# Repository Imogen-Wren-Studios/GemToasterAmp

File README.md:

# GemToasterAmp
 9v to 12v Battery Powered Amp

 _LM386 Based power amp with JFET Preamp_

 - Quality of sound highly dependent on speaker & cab combo.
 
 ## 3D Model
 #### Iso
  
 #### Underside
 
 #### Topside

 ## PCB Layout

 ## Schematic

 ### JFET Selection
 
 _I thought there were some notes on this but I can't find them, the only other thing I had read says "Anything Goes". They used cheapo out of spec parts and they worked._
 
### Other Parts slection

Some parts can be more difficult to find or I just didnt have them in stock for my test build, so these are the values I used in my *working* build:
 
 3.9k Resistors - 15k in parallel with 5.1k
 4.3k Resistors - 15k in  parallel  with 6.2k

470n Capacitor - 390n Could put an additional 100n in parallel to get closer to marked value

15n Capacitor - 22n

## Revision 0 Issues:
- Power Amp control is backwards, but this control isnt that useable, on the origional project this was replaced with a trimpot anyway, so suggest mounting it back to front for a "set and forget" control, or replace with fixed value resistor.
   - Could also look into cutting traces between 2 and 3 - TODO

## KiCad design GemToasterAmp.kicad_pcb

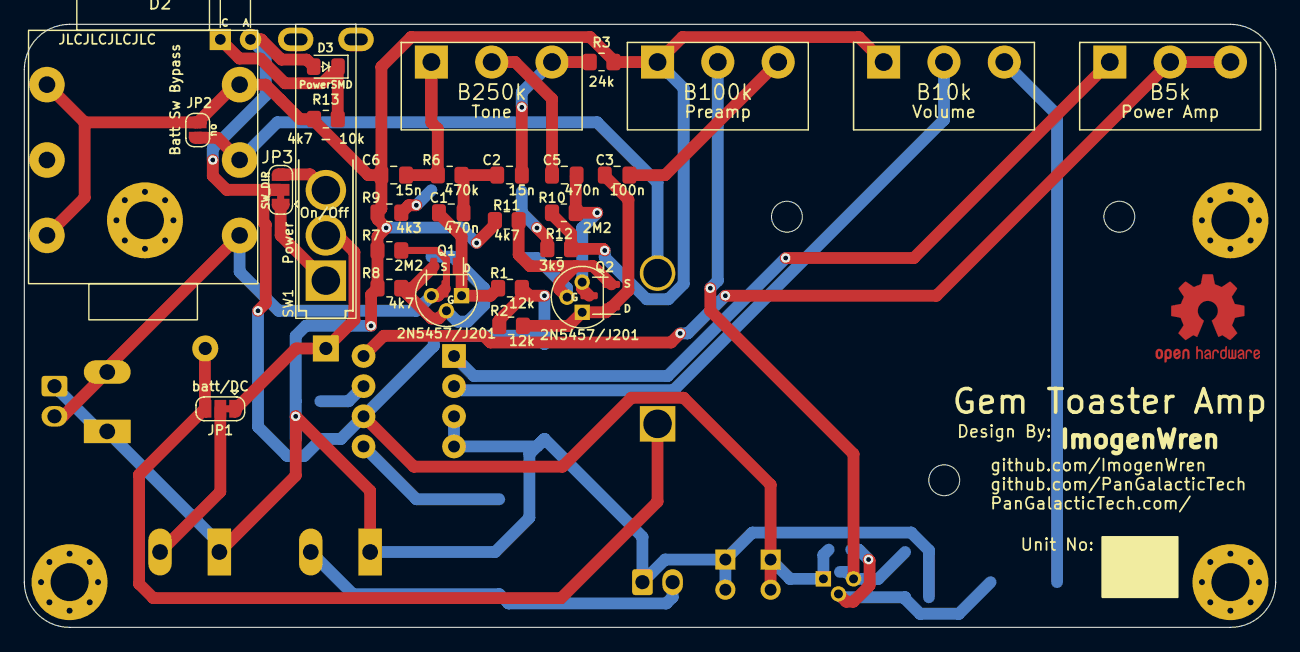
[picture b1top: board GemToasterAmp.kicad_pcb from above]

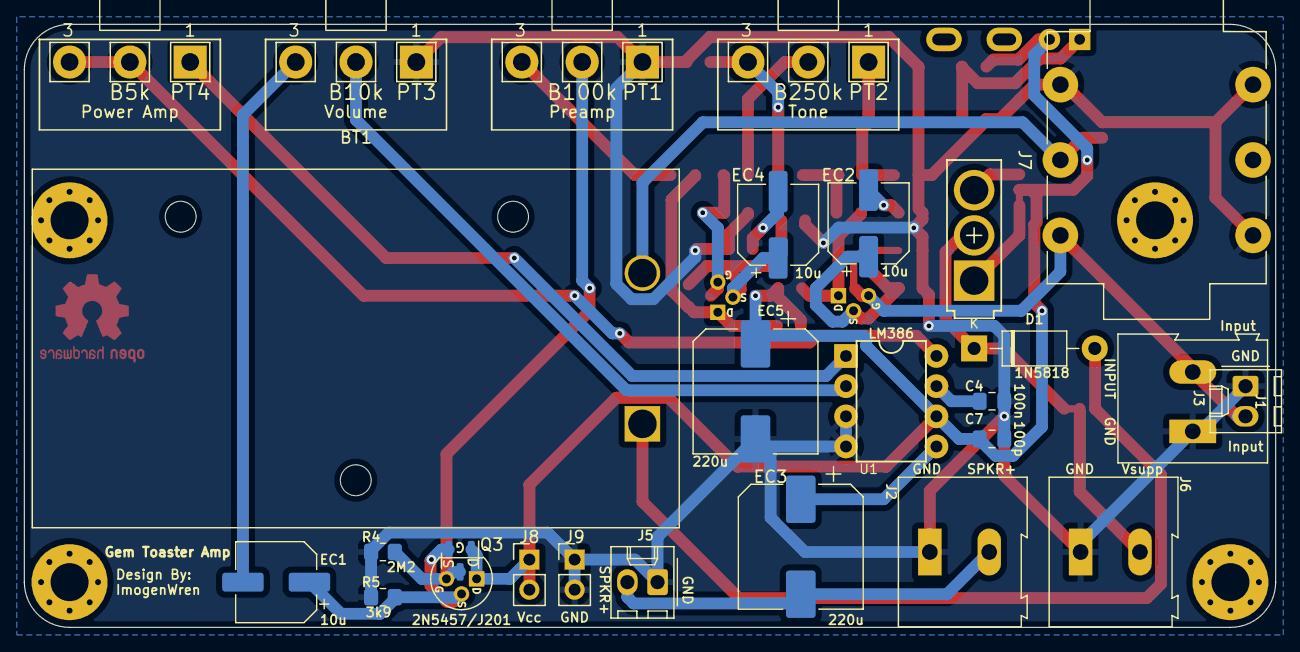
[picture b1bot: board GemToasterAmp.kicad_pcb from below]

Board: 2 copper layers, 105.4 x 50.8 mm, 49 parts (25 on the bottom side), 31 nets.

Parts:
BT1: 9v Battery; BatteryHolder_Eagle_12BH611-GR
C1, C5: 470n; C_0805_2012Metric_Pad1.18x1.45mm_HandSolder
C2, C6: 15n; C_0805_2012Metric_Pad1.18x1.45mm_HandSolder
C3, C4: 100n; C_0805_2012Metric_Pad1.18x1.45mm_HandSolder
C7: 100p; C_0805_2012Metric_Pad1.18x1.45mm_HandSolder
D1: 1N5818; D_DO-41_SOD81_P10.16mm_Horizontal
D2: PowerTH; LED_D5.0mm_Flat
D3: PowerSMD; LED_0805_2012Metric_Pad1.15x1.40mm_HandSolder
EC1, EC2, EC4: 10u; CP_Elec_6.3x5.9
EC3, EC5: 220u; CP_Elec_10x10
J1: Input; TerminalBlock_Altech_AK300-2_P5.00mm
J2: Speaker(2-8 ohm); TerminalBlock_Altech_AK300-2_P5.00mm
J3: Input; Molex_KK-254_AE-6410-02A_1x02_P2.54mm_Vertical_copy
J5: Speaker; Molex_KK-254_AE-6410-02A_1x02_P2.54mm_Vertical_copy
J6: Power; TerminalBlock_Altech_AK300-2_P5.00mm
J7: AudioJack3_Switch; Jack_6.35mm_Neutrik_NMJ6HFD2_Horizontal
J8: Vcc; PinHeader_1x02_P2.54mm_Vertical
J9: GND; PinHeader_1x02_P2.54mm_Vertical
JP1: batt/DC; SolderJumper-3_P1.3mm_Bridged12_RoundedPad1.0x1.5mm
JP2: Batt Sw Bypass; SolderJumper-2_P1.3mm_Open_RoundedPad1.0x1.5mm
JP3: SW_DIR; SolderJumper-3_P1.3mm_Bridged12_RoundedPad1.0x1.5mm
PT1: B100k; 16MM_AngleMount
PT2: B250k; 16MM_AngleMount
PT3: B10k; 16MM_AngleMount
PT4: B5k; 16MM_AngleMount
Q1, Q2, Q3: 2N5457/J201; JFET Dual Foot
R1, R2: 12k; Resistor_0805_2012_handsolder
R3: 24k; Resistor_0805_2012_handsolder
R4, R7, R10: 2M2; Resistor_0805_2012_handsolder
R5, R12: 3k9; Resistor_0805_2012_handsolder
R6: 470k; Resistor_0805_2012_handsolder
R8, R11: 4k7; Resistor_0805_2012_handsolder
R9: 4k3; Resistor_0805_2012_handsolder
R13: 4k7 - 10k; Resistor_0805_2012_handsolder
SW1: On/Off; SPDT-100SP4T1-Right-Angle
U1: LM386; DIL8

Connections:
+BATT: BT1.1 (+), D1.2 (A), JP1.3 (B)
-BATT: BT1.2 (-), J7.R, JP2.2 (B)
/INPUT: J1.2, J3.2, J7.T, Q1.3 (G), R7.1
/SPKR+: EC3.2, J2.2, J5.2
/Vsupp: J6.2, JP1.2 (C)
/power_in: D1.1 (K), JP1.1 (A), SW1.2 (B)
GND: C4.1, C6.2, C7.2, EC5.2, J1.1, J2.1, J3.1, J5.1, J6.1, J7.S, J7.SN, J7.TN, J9.1, J9.2, JP2.1 (A), PT1.1, PT3.1, R3.2, R4.2, R5.2, R7.2, R8.2, R9.2, R10.2, R11.2, R12.2, R13.1, U1.3 (+), U1.4 (GND)
unnamed: C1.1, Q1.1 (D), R1.2
unnamed: C1.2, C2.2, R6.1
unnamed: C2.1, PT2.3, R3.1
unnamed: C3.1, Q2.1 (D), R2.2
unnamed: C3.2, PT1.3
unnamed: C4.2, U1.7 (BYPASS)
unnamed: C5.1, PT2.2
unnamed: C5.2, Q2.3 (G), R10.1
unnamed: C6.1, PT2.1, R6.2
unnamed: D2.1 (K), D3.1 (K), R13.2
unnamed: EC1.1, Q3.2 (S), R5.1
unnamed: EC1.2, PT3.3
unnamed: EC2.1, Q1.2 (S), R8.1
unnamed: EC2.2, R9.1
unnamed: EC3.1, U1.5
unnamed: EC4.1, Q2.2 (S), R11.1
unnamed: EC4.2, R12.1
unnamed: PT1.2, Q3.3 (G), R4.1
unnamed: PT3.2, U1.2 (-)
unnamed: PT4.1, U1.1 (GAIN)
unnamed: PT4.2, PT4.3, U1.8 (GAIN)
unnamed: JP3.1 (A), SW1.1 (A)
unnamed: JP3.3 (B), SW1.3 (C)
VCC: C7.1, D2.2 (A), D3.2 (A), EC5.1, J8.1, J8.2, JP3.2 (C), Q3.1 (D), R1.1, R2.1, U1.6 (V+)

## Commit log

2022-12-16 asdfsd
2022-12-17 57rty
2022-12-18 vjghdfjghf
2022-12-19 dgfhfgh
2022-12-21 layout v0.1
2022-12-21 erfdrgd
2022-12-30 dfgdfgg
2022-12-31 vghnjghj
2023-01-02 dfgdfgd
2023-01-02 yrfthd
2023-01-02 KJIXCSJIDISDS
2023-01-12 dfgfg
2023-02-02 sadf
2023-02-02 added gerbers
2023-02-02 gvhjng
2023-05-26 backup
2025-01-22 moving laptop
